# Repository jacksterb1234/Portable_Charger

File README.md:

# Portable Charger — USB-C Power Delivery PCB

A custom portable USB-C Power Delivery (PD) charger with a dedicated PD trigger circuit for negotiating output voltage. Powered from a single USB-C input and designed for compact, portable use.

## Features

- **USB-C Power Delivery** input with PD voltage negotiation trigger
- **Custom PD trigger circuit** to request a specific voltage from the source
- Compact KiCad PCB design optimized for portability
- Designed with **JLCPCB assembly** constraints in mind
- CAD enclosure files included

## Repository Structure

```
Portable_Charger/
├── Charger_Kicad/         # Main charger PCB KiCad project
├── USBC_PD_Trigger_Kicad/ # USB-C PD trigger board KiCad project
└── CAD/                   # Enclosure / mechanical CAD files
```

## How It Works

1. The **PD trigger board** negotiates a target voltage with a USB-C PD source using the CC lines
2. The negotiated voltage is passed to the **charger board** for regulation and output
3. The design runs entirely from a single USB-C cable — no barrel jacks or separate power supplies required

## Tools Used

- **KiCad** — Schematic capture and PCB layout
- **JLCPCB** — PCB fabrication and assembly
- **Fusion360 / SolidWorks** — Enclosure design

## Author

**Jackson Barber** — [github.com/jacksterb1234](https://github.com/jacksterb1234)

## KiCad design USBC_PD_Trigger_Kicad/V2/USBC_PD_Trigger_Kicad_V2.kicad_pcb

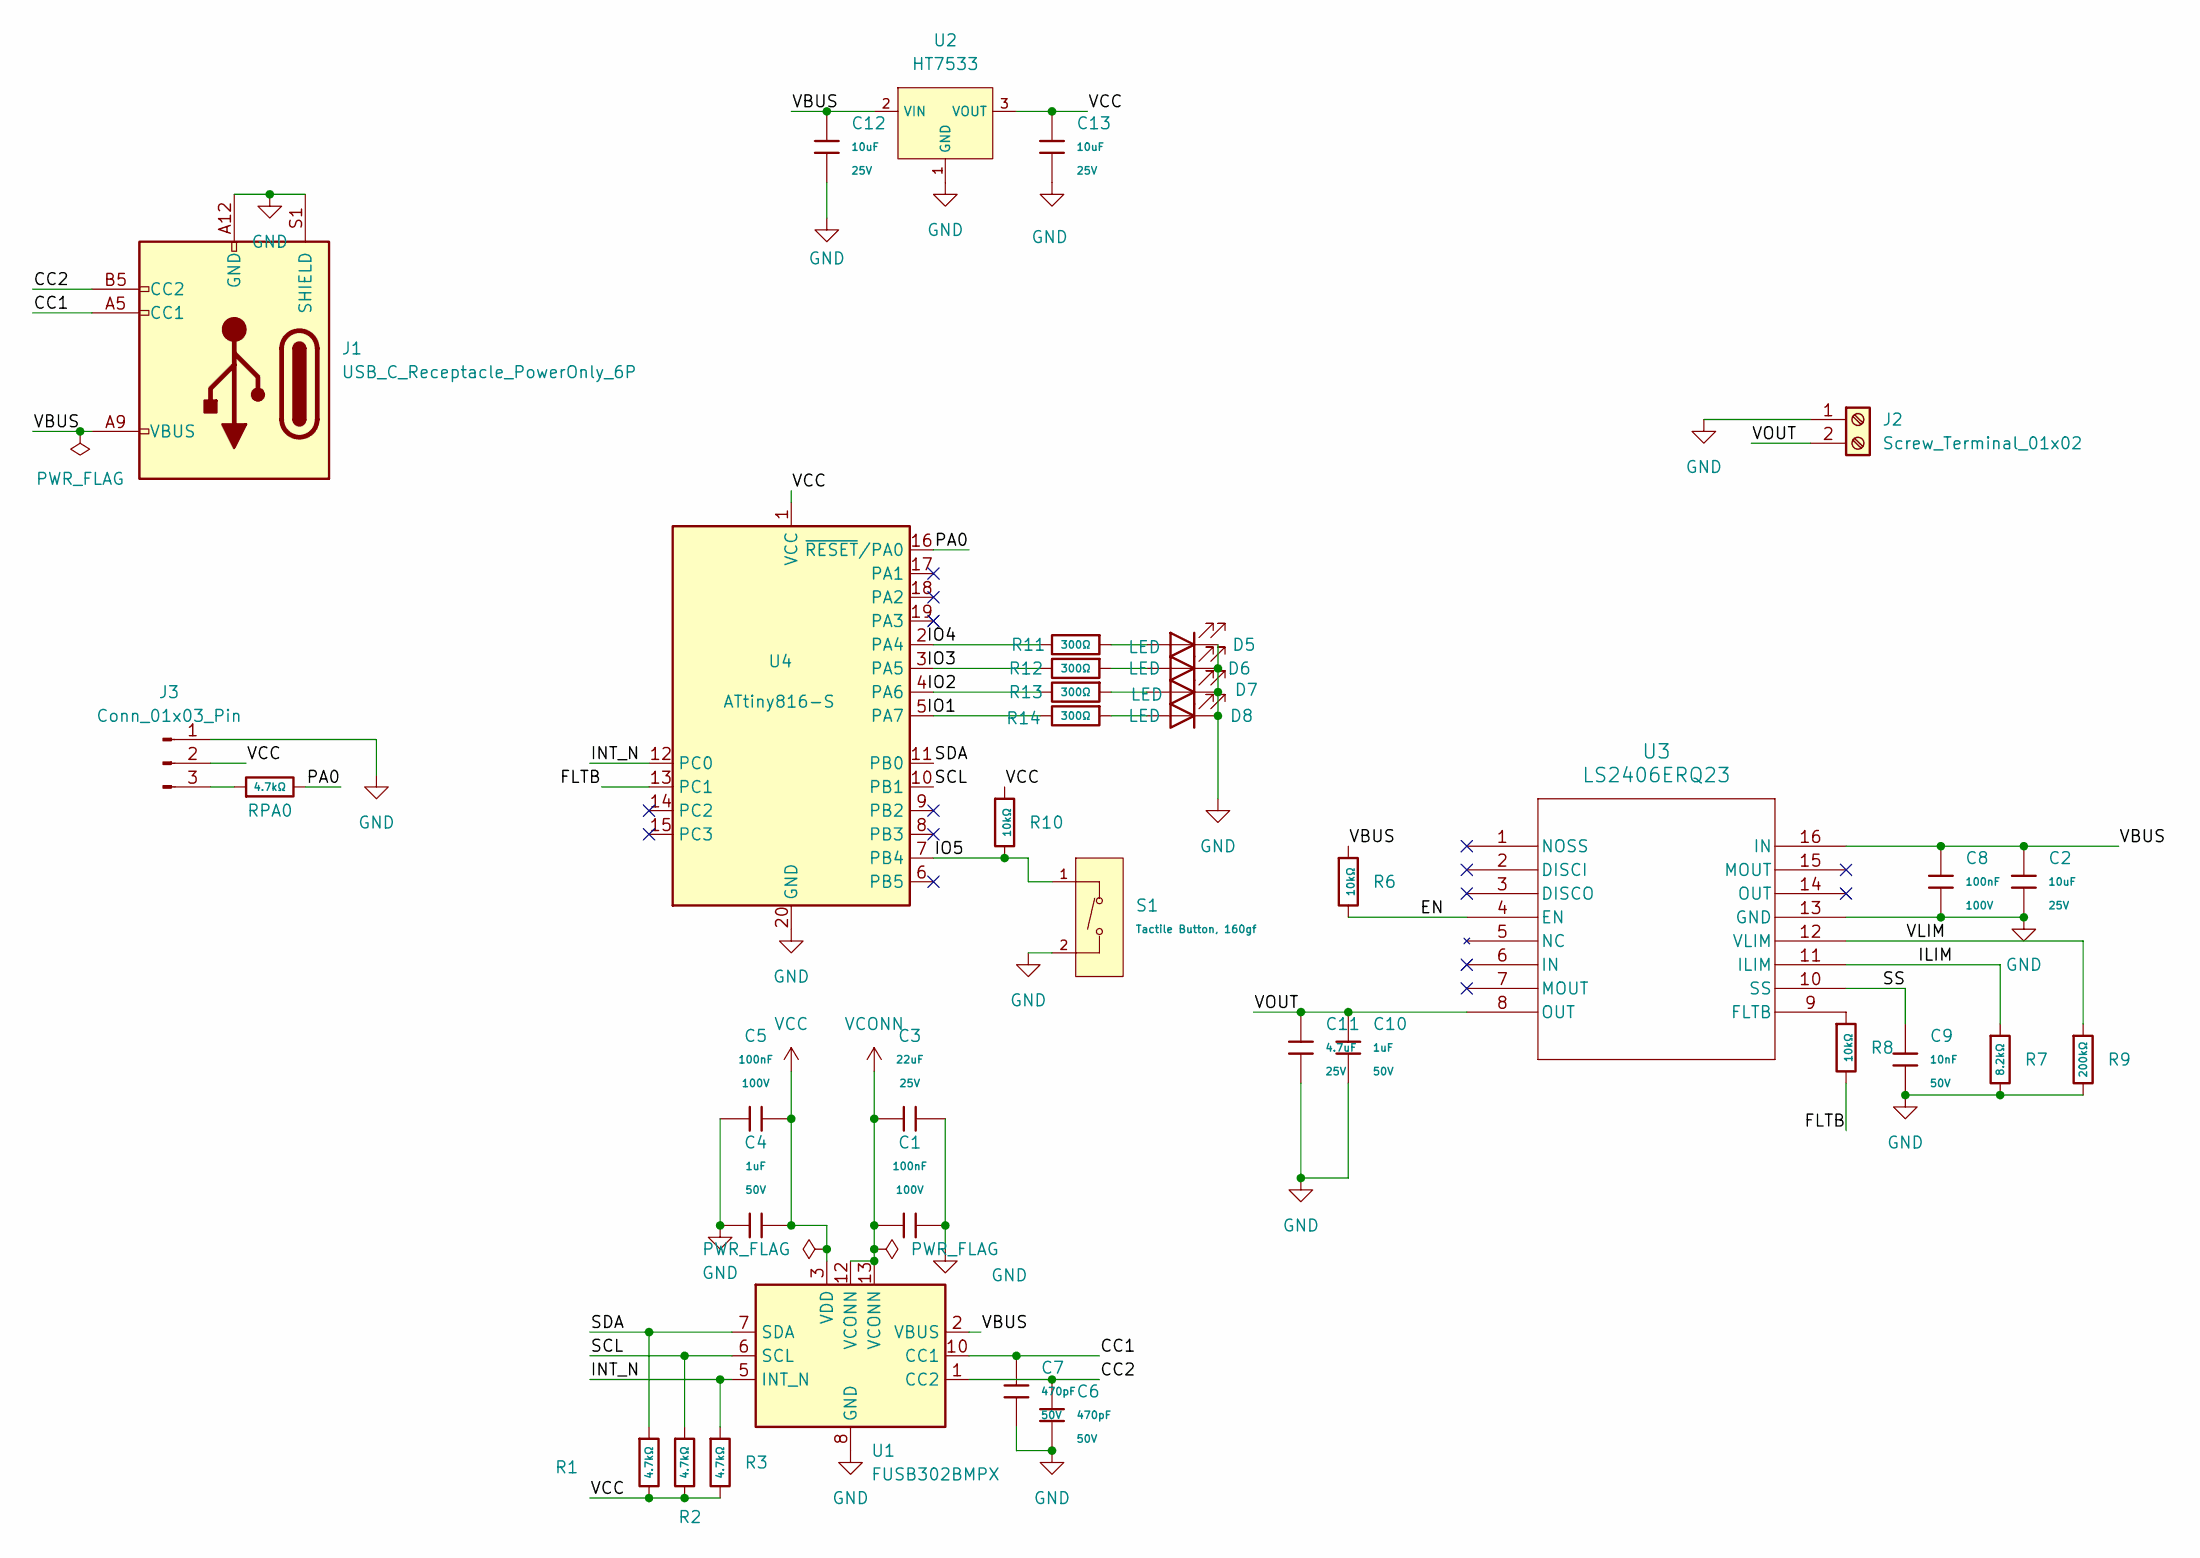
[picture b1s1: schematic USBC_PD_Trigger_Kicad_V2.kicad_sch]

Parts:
C1, C5, C8: 100nF; C_0805; Voltage Rated 100V; Tolerance ±10%; Part CL21B104KCFNNNE; LCSC C28233
C2, C12, C13: 10uF; C_0805; Voltage Rated 25V; Tolerance ±10%; Part CL21A106KAYNNNE; LCSC C15850
C3: 22uF; C_0805; Voltage Rated 25V; Tolerance ±20%; Part CL21A226MAQNNNE; LCSC C45783
C4, C10: 1uF; C_0805; Voltage Rated 50V; Tolerance ±10%; Part CL21B105KBFNNNE; LCSC C28323
C6, C7: 470pF; C_0805; Voltage Rated 50V; Tolerance ±10%; Part 0805B471K500NT; LCSC C1743
C9: 10nF; C_0805; Voltage Rated 50V; Tolerance ±10%; Part CL21B103KBANNNC; LCSC C1710
C11: 4.7uF; C_0805; Voltage Rated 25V; Tolerance ±10%; Part CL21A475KAQNNNE; LCSC C1779
D5, D6, D7, D8: LED; LED_0805_2012Metric
J1: USB_C_Receptacle_PowerOnly_6P; USB_C_Receptacle_GCT_USB4125-xx-x-0190_6P_TopMnt_Horizontal
J2: Screw_Terminal_01x02; TerminalBlock_RND_205-00045_1x02_P5.00mm_Horizontal
J3: Conn_01x03_Pin; PinHeader_1x03_P2.54mm_Vertical
R1, R2, R3: 4.7kΩ; R_0805; Overload Voltage (Max) 150V; Tolerance ±1%; Part 0805W8F4701T5E; LCSC C17673
R6, R8, R10: 10kΩ; R_0805; Overload Voltage (Max) 150V; Tolerance ±1%; Part 0805W8F1002T5E; LCSC C17414
R7: 8.2kΩ; R_0805; Overload Voltage (Max) 150V; Tolerance ±1%; Part 0805W8F8201T5E; LCSC C17828
R9: 200kΩ; R_0805; Overload Voltage (Max) 150V; Tolerance ±1%; Part 0805W8F2003T5E; LCSC C17539
R11, R12, R13, R14: 300Ω; R_0805; Overload Voltage (Max) 150V; Tolerance ±1%; Part 0805W8F3000T5E; LCSC C17617
RPA0: 4.7kΩ; R_0805; Overload Voltage (Max) 150V; Tolerance ±1%; Part 0805W8F4701T5E; LCSC C17673
S1: Tactile Button, 160gf; SW_TS-1088-AR02016; Voltage Rating (Dc) 12V; Part TS-1088-AR02016; LCSC C720477
U1: FUSB302BMPX; WQFN-14-1EP_2.5x2.5mm_P0.5mm_EP1.45x1.45mm
U2: HT7533; SOT-89-3_L4.5-W2.5-P1.50-LS4.2-BR; Output Voltage 3.3V; Dropout Voltage 55mV@(1mA); Part HT7533-1; LCSC C14289
U3: LS2406ERQ23; QFN16L_2P5X3P2-0P6_LTF
U4: ATtiny816-S; SOIC-20W_7.5x12.8mm_P1.27mm

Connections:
/CC1: C7.1, J1.A5 (CC1), U1.10 (CC1), U1.11 (CC1)
/CC2: C6.1, J1.B5 (CC2), U1.1 (CC2), U1.14 (CC2)
/EN: R6.2, U3.4 (EN)
/FLTB: R8.2, U4.13 (PC1)
/ILIM: R7.1, U3.11 (ILIM)
/INT_N: R3.1, U1.5 (INT_N), U4.12 (PC0)
/IO1: R14.2, U4.5 (PA7)
/IO2: R13.2, U4.4 (PA6)
/IO3: R12.2, U4.3 (PA5)
/IO4: R11.2, U4.2 (PA4)
/IO5: R10.2, S1.1 (A), U4.7 (PB4)
/PA0: RPA0.2, U4.16 (~RESET/PA0)
/SCL: R2.1, U1.6 (SCL), U4.10 (PB1)
/SDA: R1.1, U1.7 (SDA), U4.11 (PB0)
/SS: C9.1, U3.10 (SS)
/VBUS: C2.1, C8.1, C12.1, J1.A9 (VBUS), J1.B9 (VBUS), R6.1, U1.2 (VBUS), U2.2 (VIN), U3.16 (IN)
/VLIM: R9.1, U3.12 (VLIM)
/VOUT: C10.1, C11.1, J2.2, U3.8 (OUT)
GND: C1.2, C2.2, C3.2, C4.1, C5.2, C6.2, C7.2, C8.2, C9.2, C10.2, C11.2, C12.2, C13.2, D5.1 (K), D6.1 (K), D7.1 (K), D8.1 (K), J1.A12 (GND), J1.B12 (GND), J1.S1 (SHIELD), J2.1, J3.1, R7.2, R9.2, S1.2 (B), U1.8 (GND), U1.9 (GND), U1.15 (GND), U2.1 (GND), U3.13 (GND), U4.20 (GND)
unnamed: D5.2 (A), R11.1
unnamed: D6.2 (A), R12.1
unnamed: D7.2 (A), R13.1
unnamed: D8.2 (A), R14.1
unnamed: J3.3, RPA0.1
unnamed: R8.1, U3.9 (FLTB)
VCC: C4.2, C5.1, C13.1, J3.2, R1.2, R2.2, R3.2, R10.1, U1.3 (VDD), U1.4 (VDD), U2.3 (VOUT), U4.1 (VCC)
VCONN: C1.1, C3.1, U1.12 (VCONN), U1.13 (VCONN)

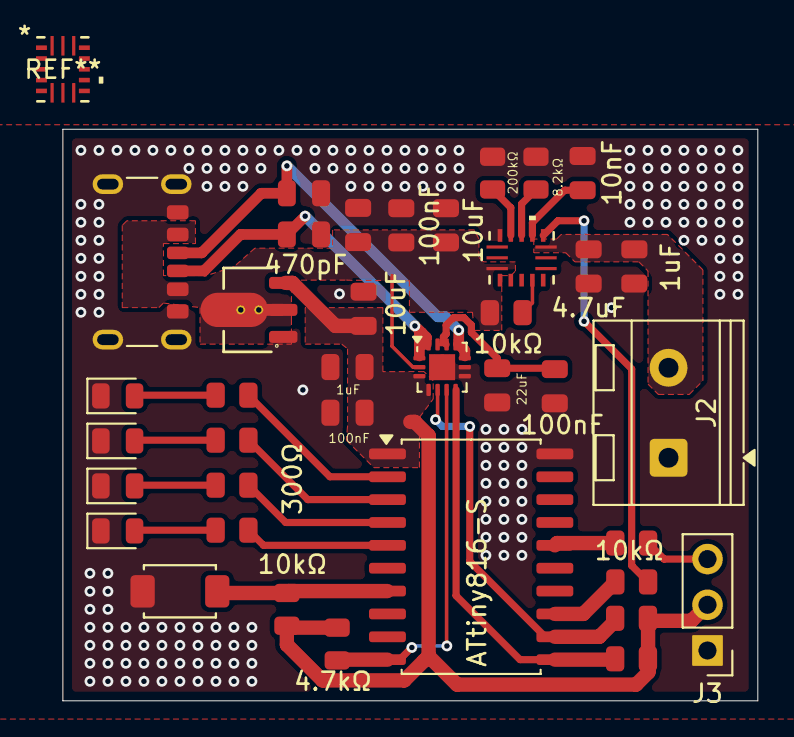
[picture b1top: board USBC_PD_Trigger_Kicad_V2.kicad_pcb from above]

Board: 2 copper layers, 38.6 x 31.7 mm, 38 parts (0 on the bottom side), 27 nets.

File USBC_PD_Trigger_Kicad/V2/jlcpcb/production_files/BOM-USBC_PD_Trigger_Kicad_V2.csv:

Comment,Designator,Footprint,LCSC,Quantity
100nF,"C1,C5,C8",C_0805,C28233,3
10kΩ,"R10,R6,R8",R_0805,C17414,3
10nF,C9,C_0805,C1710,1
10uF,"C12,C13,C2",C_0805,C15850,3
1uF,"C10,C4",C_0805,C28323,2
200kΩ,R9,R_0805,C17539,1
22uF,C3,C_0805,C45783,1
300Ω,"R11,R12,R13,R14",R_0805,C17617,4
4.7kΩ,"R1,R2,R3,RPA0",R_0805,C17673,4
4.7uF,C11,C_0805,C1779,1
470pF,"C6,C7",C_0805,C1743,2
8.2kΩ,R7,R_0805,C17828,1
ATtiny816-S,U4,SOIC-20W_7.5x12.8mm_P1.27mm,C2054204,1
FUSB302BMPX,U1,WQFN-14-1EP_2.5x2.5mm_P0.5mm_EP1.45x1.45mm,C132291,1
HT7533,U2,SOT-89-3_L4.5-W2.5-P1.50-LS4.2-BR,C14289,1
LED,D5,LED_0805_2012Metric,C2297,1
LS2406ERQ23,U3,QFN16L_2P5X3P2-0P6_LTF,C5355481,1
Screw_Terminal_01x02,J2,TerminalBlock_RND_205-00045_1x02_P5.00mm_Horizontal,C3703,1
"Tactile Button, 160gf",S1,SW_TS-1088-AR02016,C720477,1
USB_C_Receptacle_PowerOnly_6P,J1,USB_C_Receptacle_GCT_USB4125-xx-x-0190_6P_TopMnt_Horizontal,C7507406,1
Conn_01x03_Pin,J3,PinHeader_1x03_P2.54mm_Vertical,,1
LED,D7,LED_0805_2012Metric,,1
LED,D8,LED_0805_2012Metric,,1
LED,D6,LED_0805_2012Metric,,1

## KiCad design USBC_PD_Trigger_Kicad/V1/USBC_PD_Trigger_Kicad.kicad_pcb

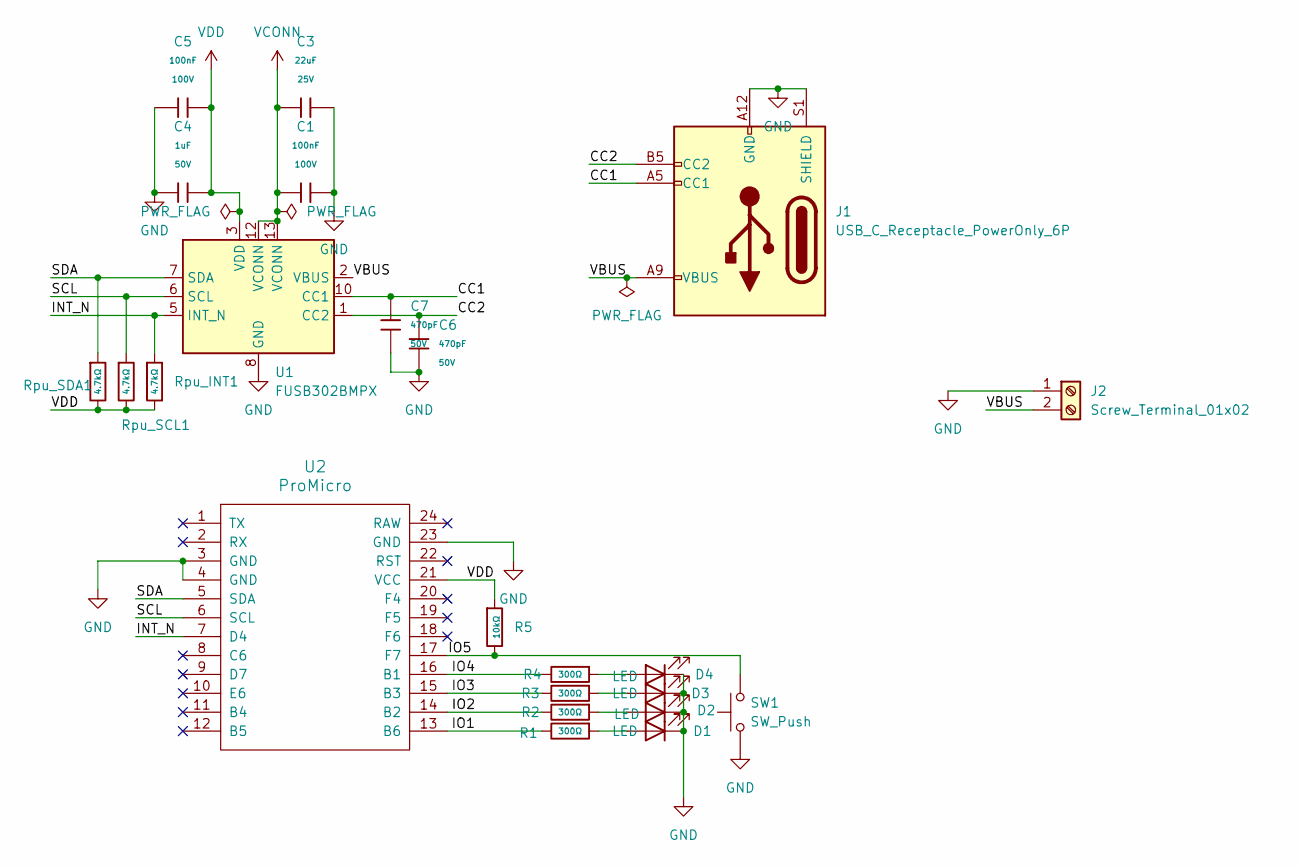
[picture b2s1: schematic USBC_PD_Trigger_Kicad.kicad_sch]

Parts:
C1, C5: 100nF; C_0805; Voltage Rated 100V; Tolerance ±10%; Part CL21B104KCFNNNE; LCSC C28233
C3: 22uF; C_0805; Voltage Rated 25V; Tolerance ±20%; Part CL21A226MAQNNNE; LCSC C45783
C4: 1uF; C_0805; Voltage Rated 50V; Tolerance ±10%; Part CL21B105KBFNNNE; LCSC C28323
C6, C7: 470pF; C_0805; Voltage Rated 50V; Tolerance ±10%; Part 0805B471K500NT; LCSC C1743
D1, D2, D3, D4: LED; LED_0805_2012Metric
J1: USB_C_Receptacle_PowerOnly_6P; USB_C_Receptacle_GCT_USB4125-xx-x-0190_6P_TopMnt_Horizontal
J2: Screw_Terminal_01x02; TerminalBlock_RND_205-00045_1x02_P5.00mm_Horizontal
R1, R2, R3, R4: 300Ω; R_0805; Overload Voltage (Max) 150V; Tolerance ±1%; Part 0805W8F3000T5E; LCSC C17617
R5: 10kΩ; R_0805; Overload Voltage (Max) 150V; Tolerance ±1%; Part 0805W8F1002T5E; LCSC C17414
Rpu_INT1: 4.7kΩ; R_0805; Overload Voltage (Max) 150V; Tolerance ±1%; Part 0805W8F4701T5E; LCSC C17673
Rpu_SCL1: 4.7kΩ; R_0805; Overload Voltage (Max) 150V; Tolerance ±1%; Part 0805W8F4701T5E; LCSC C17673
Rpu_SDA1: 4.7kΩ; R_0805; Overload Voltage (Max) 150V; Tolerance ±1%; Part 0805W8F4701T5E; LCSC C17673
SW1: SW_Push; SW_SPST_PTS645
U1: FUSB302BMPX; WQFN-14-1EP_2.5x2.5mm_P0.5mm_EP1.45x1.45mm
U2: ProMicro

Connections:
/CC1: C7.1, J1.A5 (CC1), U1.10 (CC1), U1.11 (CC1)
/CC2: C6.1, J1.B5 (CC2), U1.1 (CC2), U1.14 (CC2)
/INT_N: Rpu_INT1.1, U1.5 (INT_N), U2.7 (D4)
/IO1: R1.2, U2.13 (B6)
/IO2: R2.2, U2.14 (B2)
/IO3: R3.2, U2.15 (B3)
/IO4: R4.2, U2.16 (B1)
/IO5: R5.2, SW1.2, U2.17 (F7)
/SCL: Rpu_SCL1.1, U1.6 (SCL), U2.6 (SCL)
/SDA: Rpu_SDA1.1, U1.7 (SDA), U2.5 (SDA)
/VBUS: J1.A9 (VBUS), J1.B9 (VBUS), J2.2, U1.2 (VBUS)
GND: C1.2, C3.2, C4.1, C5.2, C6.2, C7.2, D1.1 (K), D2.1 (K), D3.1 (K), D4.1 (K), J1.A12 (GND), J1.B12 (GND), J1.S1 (SHIELD), J2.1, SW1.1, U1.8 (GND), U1.9 (GND), U1.15 (GND), U2.3 (GND), U2.4 (GND), U2.23 (GND)
unnamed: D1.2 (A), R1.1
unnamed: D2.2 (A), R2.1
unnamed: D3.2 (A), R3.1
unnamed: D4.2 (A), R4.1
VCONN: C1.1, C3.1, U1.12 (VCONN), U1.13 (VCONN)
VDD: C4.2, C5.1, R5.1, Rpu_INT1.2, Rpu_SCL1.2, Rpu_SDA1.2, U1.3 (VDD), U1.4 (VDD), U2.21 (VCC)

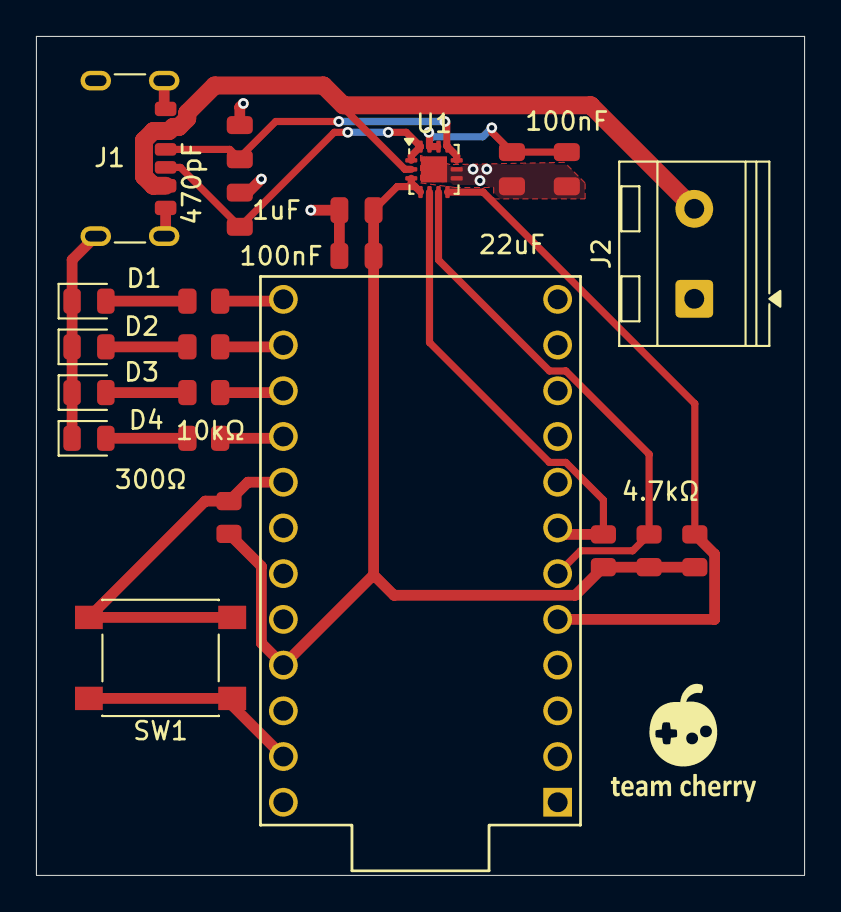
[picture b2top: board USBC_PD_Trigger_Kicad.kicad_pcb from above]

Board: 2 copper layers, 42.7 x 46.6 mm, 23 parts (0 on the bottom side), 18 nets.

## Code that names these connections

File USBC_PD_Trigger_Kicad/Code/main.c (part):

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// ========== PIN ASSIGNMENTS ==========
#define LED_PORT         PORTA
#define LED_DDR          DDRA
#define LED_PIN_1        PA7
#define LED_PIN_2        PA6
#define LED_PIN_3        PA5
#define LED_PIN_4        PA4
#define LED_MASK         ((1<<PA7)|(1<<PA6)|(1<<PA5)|(1<<PA4))

#define BUTTON_PORT      PORTB
#define BUTTON_PIN_REG   PINB
#define BUTTON_DDR       DDRB
#define BUTTON_PIN       PB4

#define FLTB_PORT        PORTC
#define FLTB_PIN_REG     PINC
#define FLTB_DDR         DDRC
#define FLTB_PIN         PC1

#define FUSB_INT_PORT    PORTC
#define FUSB_INT_PIN_REG PINC
#define FUSB_INT_DDR     DDRC
#define FUSB_INT_PIN     PC0

#define I2C_SCL_PORT     PORTB
#define I2C_SCL_PIN_REG  PINB
#define I2C_SCL_DDR      DDRB
#define I2C_SCL_PIN      PB1

#define I2C_SDA_PORT     PORTB
#define I2C_SDA_PIN_REG  PINB
#define I2C_SDA_DDR      DDRB
#define I2C_SDA_PIN      PB0

// ========== FUSB302B REGISTERS ==========
#define FUSB_ADDR           0x44    // I2C write address (0x22 << 1)
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    
    uint8_t mask = 0;
    for (uint8_t i = 0; i <= voltage_idx; i++) {
        mask |= (1 << (PA7 - i));
    }
    LED_PORT = (LED_PORT & ~LED_MASK) | (mask & LED_MASK);
}
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}

static void fault_init(void) {
    FLTB_DDR &= ~(1 << FLTB_PIN);
    FLTB_PORT |= (1 << FLTB_PIN);  // pullup
}

static void fusb_int_init(void) {
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}

static bool fault_is_active(void) {
    return !(FLTB_PIN_REG & (1 << FLTB_PIN));
}

static bool fusb_has_interrupt(void) {
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
// ========== MAIN LOOP & INTERRUPT HANDLERS ==========
ISR(PCINT0_vect) {
    // portB changes: button (PB4) + i2c (PB0, PB1)
    static uint8_t btn_count = 0;
    if (button_is_pressed()) {
        btn_count++;
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}

ISR(PCINT1_vect) {
    // portC changes: FUSB INT (PC0) + FLTB (PC1)
    if (fusb_has_interrupt()) {
        fusb_interrupt = true;
    }
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    leds_init();
    
    // Pin change interrupts
    PCMSK0 = (1 << PCINT4);  // Button on PB4
    PCMSK1 = (1 << PCINT8) | (1 << PCINT9);  // PC0 (FUSB INT) and PC1 (FLTB)
    GIMSK = (1 << PCIE0) | (1 << PCIE1);
    
    sei();
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
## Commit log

2026-02-10 Initial commit, PCB and Schem WIP
2026-02-11 Updated to use ISP5328P breakout, created initial case CAD
2026-02-28 Created PD trigger mechanismx
2026-03-02 Added V2 of trigger board w efuse and smaller mc
2026-03-05 Updated Pd trigger to use only 1 cable
2026-03-28 Added Code
2026-05-30 Add README
    Added detailed project description, features, repository structure, operation steps, tools used, and author information.
